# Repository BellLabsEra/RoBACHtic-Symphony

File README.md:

# RoBACHtic-Symphony
ECE 3011 Design Fundamentals Project

## Project Description

In the realm of junior-design team initiatives, we undertook a project focused on the development of an educational robot kit. This kit, specifically designed for 5th-grade students, imparts comprehensive knowledge on discerning a violin's bow movement, placement, and techniques—particularly bow posture—while performing musical compositions featuring diverse notes. The device seamlessly integrates with a MIDI piano keyboard, utilizing user input to produce two outputs: a robotic arm executing bow movements corresponding to the "mapped" string and an audio sample replicating the played note.

Comprising a team of four students—three specializing in Electrical Engineering and one in Computer Engineering—we dedicated ourselves to the intricate aspects of Mechanical, Electrical, and Software engineering. In conjunction with the hardware and software components, we meticulously crafted four essential artifacts: a Design Document, Bill of Materials (BOM), Lesson Plan, and Notebook. Notably, our Lesson Plan aligns meticulously with the Georgia Standards of Excellence (GSE) for both Music and Computer Science curricula.

In the context of this collaborative effort, I assumed a leadership role in spearheading the software development aspect of the project. This multifaceted undertaking served as the focal point of our endeavors within the framework of ECE 3011 - Design Fundamentals.

### Link to YouTube Video Demonstration: 
https://youtu.be/gud--ybyr-s?si=2pJu3Hc5zI2o3BWv

### Link to Final Document PDF: 
https://github.com/BellLabsEra/RoBACHtic-Symphony/blob/main/ECE3011%20Team%20C2%20Final%20Document%20Package.pdf

Document containing the (1) Design Document,(2) Lesson Plan, and (3) BOM

### Front View Pictures:

### Labeled Picture:

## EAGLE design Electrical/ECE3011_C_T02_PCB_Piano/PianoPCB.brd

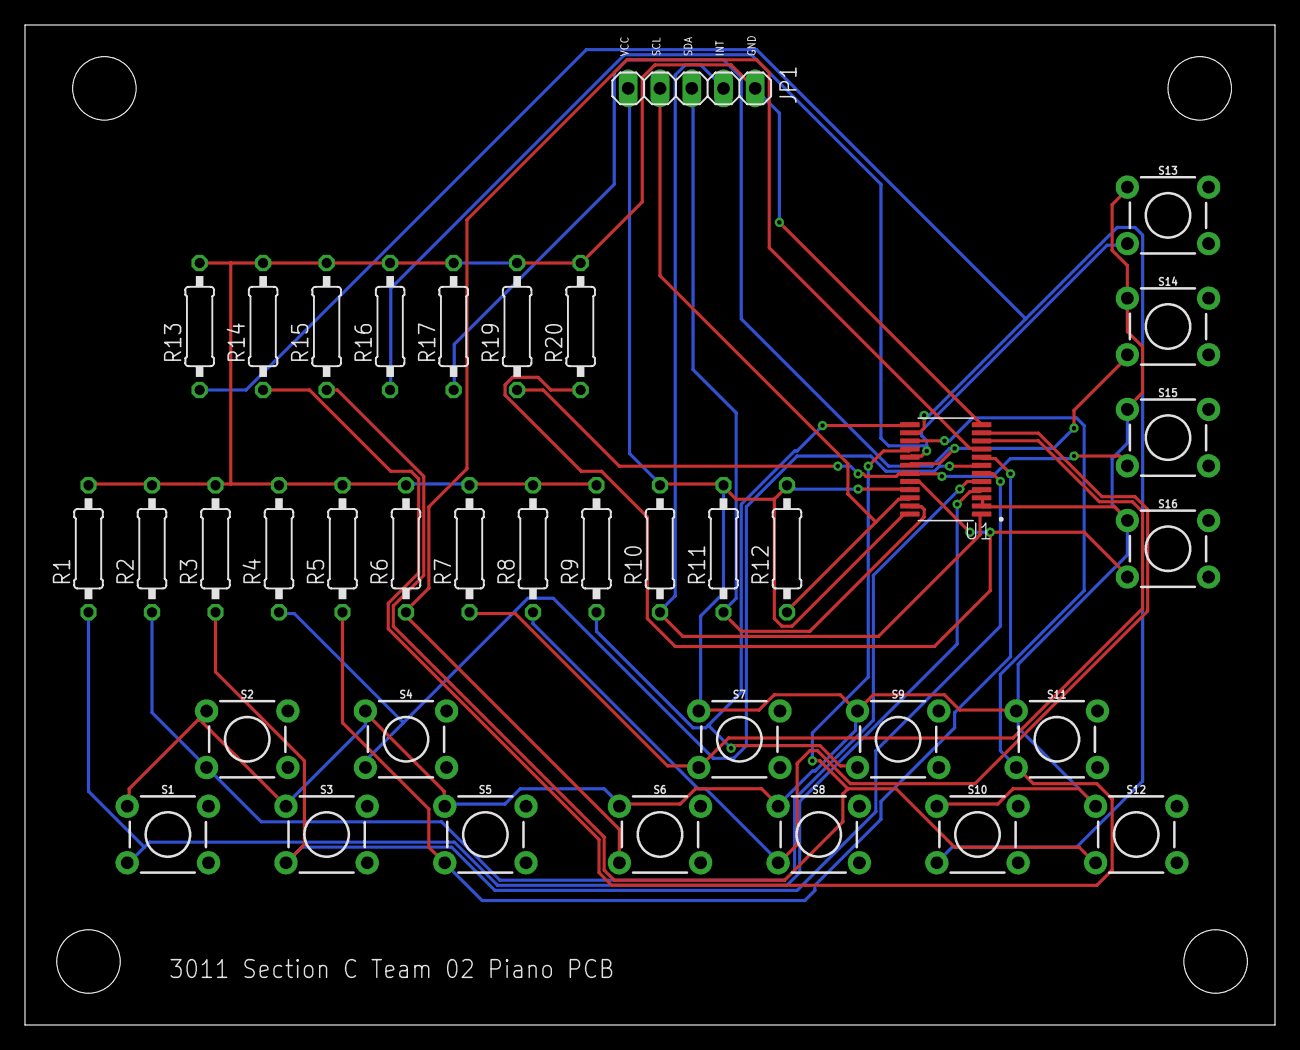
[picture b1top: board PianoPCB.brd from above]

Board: 2 copper layers, 100.0 x 80.0 mm, 37 parts (0 on the bottom side), 21 nets.

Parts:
JP1: 1X05
R1, R2, R3, R4, R5, R6, R7, R8, R9, R10, R11, R12, R13, R14, R15, R16, R17, R19, R20: 10k; 0207/10
S1, S2, S3, S4, S5, S6, S7, S8, S9, S10, S11, S12, S13, S14, S15, S16: MOMENTARY-SWITCH-SPST-PTH-6.0MM; TACTILE_SWITCH_PTH_6.0MM
U1: PCF8575PWE4; SOP65P640X120-24N

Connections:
GND: JP1.5, R1.2, R2.2, R3.2, R4.2, R5.2, R6.2, R7.2, R8.2, R9.2, R13.2, R14.2, R15.2, R16.2, R17.2, R19.2, R20.2, U1.12
unnamed: JP1.4, R10.1, U1.1
unnamed: R1.1, S1.3, U1.4
unnamed: R2.1, S2.3, U1.5
unnamed: R3.1, S3.3, U1.6
unnamed: R4.1, S4.3, U1.7
unnamed: R5.1, S5.3, U1.8
unnamed: R6.1, S6.3, U1.9
unnamed: R7.1, S7.3, U1.10
unnamed: R8.1, S8.3, U1.11
unnamed: R16.1, S13.3, U1.17
unnamed: JP1.3, R11.1, U1.23
unnamed: JP1.2, R12.1, U1.22
unnamed: R17.1, S14.3, U1.18
unnamed: R20.1, S16.3, U1.20
unnamed: R19.1, S15.3, U1.19
unnamed: R14.1, S11.3, U1.15
unnamed: R9.1, S9.3, U1.13
unnamed: R13.1, S10.3, U1.14
unnamed: R15.1, S12.3, U1.16
VCC1: JP1.1, R10.2, R11.2, R12.2, S1.1, S2.1, S3.1, S4.1, S5.1, S6.1, S7.1, S8.1, S9.1, S10.1, S11.1, S12.1, S13.1, S14.1, S15.1, S16.1, U1.2, U1.3, U1.21, U1.24

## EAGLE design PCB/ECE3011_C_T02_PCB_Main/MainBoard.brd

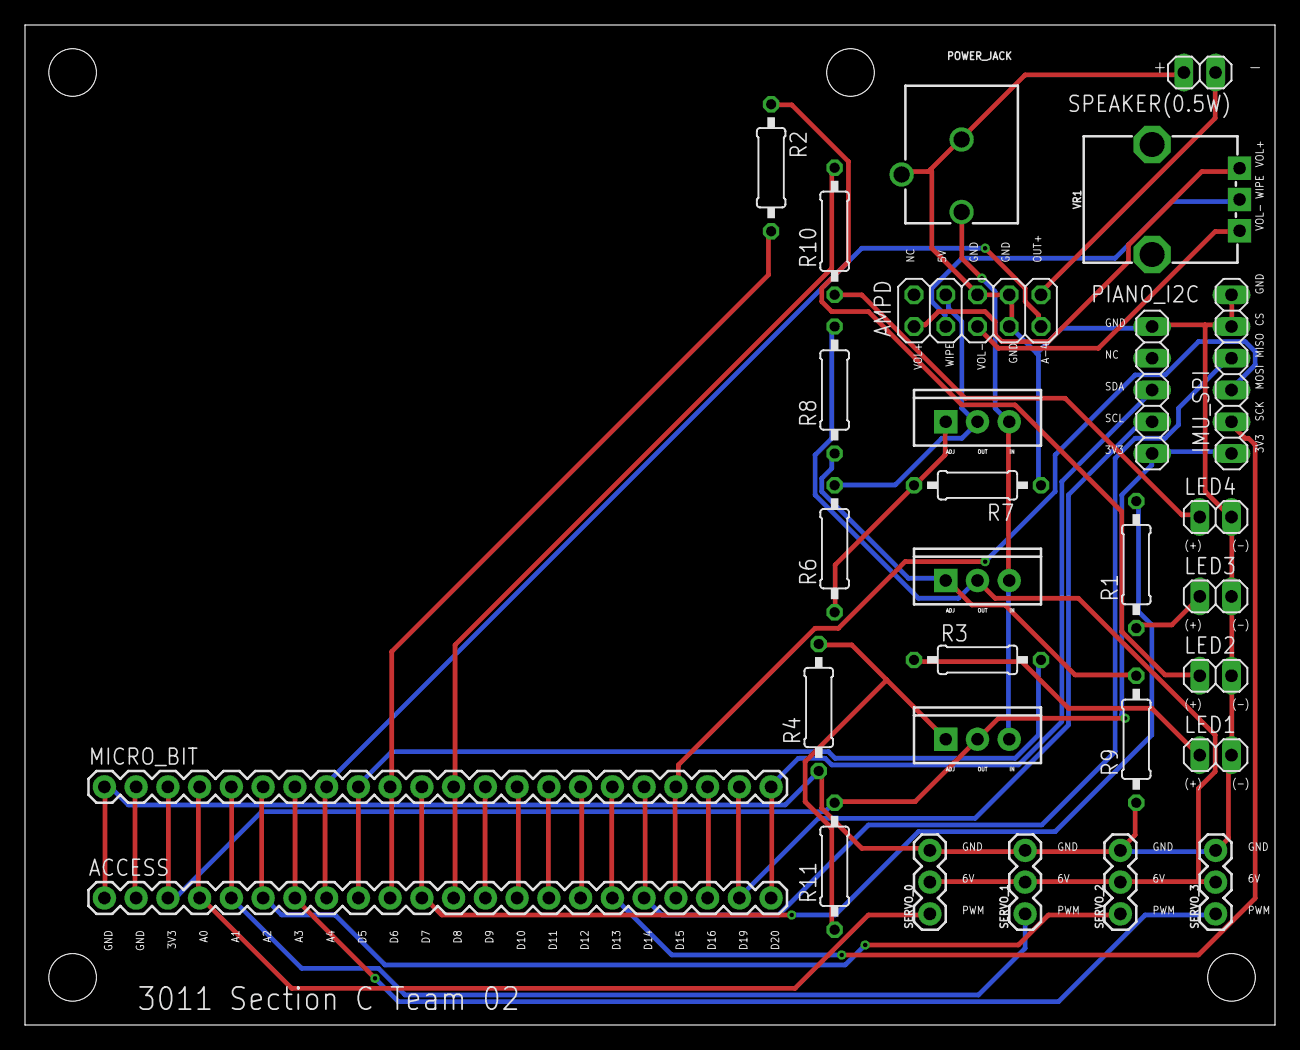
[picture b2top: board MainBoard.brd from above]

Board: 2 copper layers, 100.0 x 80.0 mm, 29 parts (0 on the bottom side), 36 nets.

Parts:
ACCESS: CONN_22_PTH; 1X22
AMPD: 2X05
IMU_SPI: 1X06
LED1, LED2, LED3, LED4: 1X02
MICRO_BIT: CONN_22_PTH; 1X22
PIANO_I2C: 1X05
POWER_JACK: POWER_JACKPTH_BREAD; POWER_JACK_PTH_BREAD
R1, R2, R3, R7, R10: 750; 0207/10
R4: 1.8k; 0207/10
R6: 240; 0207/10
R8: 715; 0207/10
R9: 2.7k; 0207/10
R11: 470; 0207/10
SERVO_0, SERVO_1, SERVO_2, SERVO_3: SERVO; 1X03
SPEAKER(0.5W): 1X02
VR1: 10k; POT-PTH-ALPS
VREG1, VREG2, VREG3: V_REG_317SINK; TO220-ADJ

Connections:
3V3: ACCESS.3, IMU_SPI.1, MICRO_BIT.3, PIANO_I2C.1, R11.2, VREG1.OUT
5V: AMPD.7, R6.2, VREG2.OUT
6V: R8.2, SERVO_0.2, SERVO_1.2, SERVO_2.2, SERVO_3.2, VREG3.OUT
A-0: ACCESS.4, MICRO_BIT.4, SERVO_0.1
A-1: ACCESS.5, MICRO_BIT.5, SERVO_1.1
A-2: ACCESS.6, MICRO_BIT.6, SERVO_2.1
A-3: ACCESS.7, MICRO_BIT.7, SERVO_3.1
A-4: ACCESS.8, AMPD.2, MICRO_BIT.8
D-5: ACCESS.9, MICRO_BIT.9, R3.2
D-6: ACCESS.10, MICRO_BIT.10, R2.2
D-7: ACCESS.11, MICRO_BIT.11, R1.2
D-8: ACCESS.12, MICRO_BIT.12, R10.2
D-9: ACCESS.13, MICRO_BIT.13
D-10: ACCESS.14, MICRO_BIT.14
D-11: ACCESS.15, MICRO_BIT.15
D-12: ACCESS.16, MICRO_BIT.16
D-13: ACCESS.17, IMU_SPI.2, MICRO_BIT.17
D-14: ACCESS.18, IMU_SPI.4, MICRO_BIT.18
D-15: ACCESS.19, IMU_SPI.3, MICRO_BIT.19
D-16: ACCESS.20, MICRO_BIT.20
D-19: ACCESS.21, MICRO_BIT.21, PIANO_I2C.2
D-20: ACCESS.22, MICRO_BIT.22, PIANO_I2C.3
GND1: ACCESS.1, AMPD.3, AMPD.4, AMPD.5, IMU_SPI.5, IMU_SPI.6, LED1.2, LED2.2, LED3.2, LED4.2, MICRO_BIT.1, PIANO_I2C.5, POWER_JACK.GND, POWER_JACK.GNDBREAK, R4.1, R7.1, R9.1, SERVO_0.3, SERVO_1.3, SERVO_2.3, SERVO_3.3, SPEAKER(0.5W).2
GND2: ACCESS.2, MICRO_BIT.2
MAIN6V: POWER_JACK.PWR, VREG1.IN, VREG2.IN, VREG3.IN
unnamed: LED1.1, R3.1
unnamed: LED2.1, R2.1
unnamed: LED3.1, R1.1
unnamed: LED4.1, R10.1
unnamed: R4.2, R11.1, VREG1.ADJ
unnamed: R6.1, R7.2, VREG2.ADJ
unnamed: R8.1, R9.2, VREG3.ADJ
OUT+: AMPD.1, SPEAKER(0.5W).1
VOL+: AMPD.10, VR1.P$3
VOL-: AMPD.6, VR1.P$1
WIPE: AMPD.8, VR1.P$2

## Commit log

2023-10-05 Scaling Down Main Box
2023-10-05 Mechanical Update
2023-10-12 Added a StateMachine Python File
2023-10-12 Added a Software Folder
2023-10-12 renamed the PCB Folder to Electrical
2023-10-13 Added SinglePushButtonDemo to the Software folder
2023-10-31 Created a Hardware and Software functionality test via C++ program that runs on an Arduino Mega 2560. This program takes in 12 Digital GPIO inputs from a Piano Keyboard model with 12 pushbuttons and 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
2024-01-20 updated readme with a description block, link to youtube video demo, and uploaded the Final Document PDF
2024-01-21 addind images to the repo
2024-01-21 embeddeing image link into readme
2024-01-21 retried embeddeing image link into readme
2024-01-21 added Microbit Code repo as folder & zip file within the the Software Folder

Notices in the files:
parts and their libraries:
SparkFun-Switches: Licensing: Creative Commons ShareAlike 4.0 International - https://creativecommons.org/licenses/by-sa/4.0
